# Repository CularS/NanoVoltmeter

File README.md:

# NanoVoltmeter
Low and high input resistance nanovoltmeter with 20 and 200 mV range

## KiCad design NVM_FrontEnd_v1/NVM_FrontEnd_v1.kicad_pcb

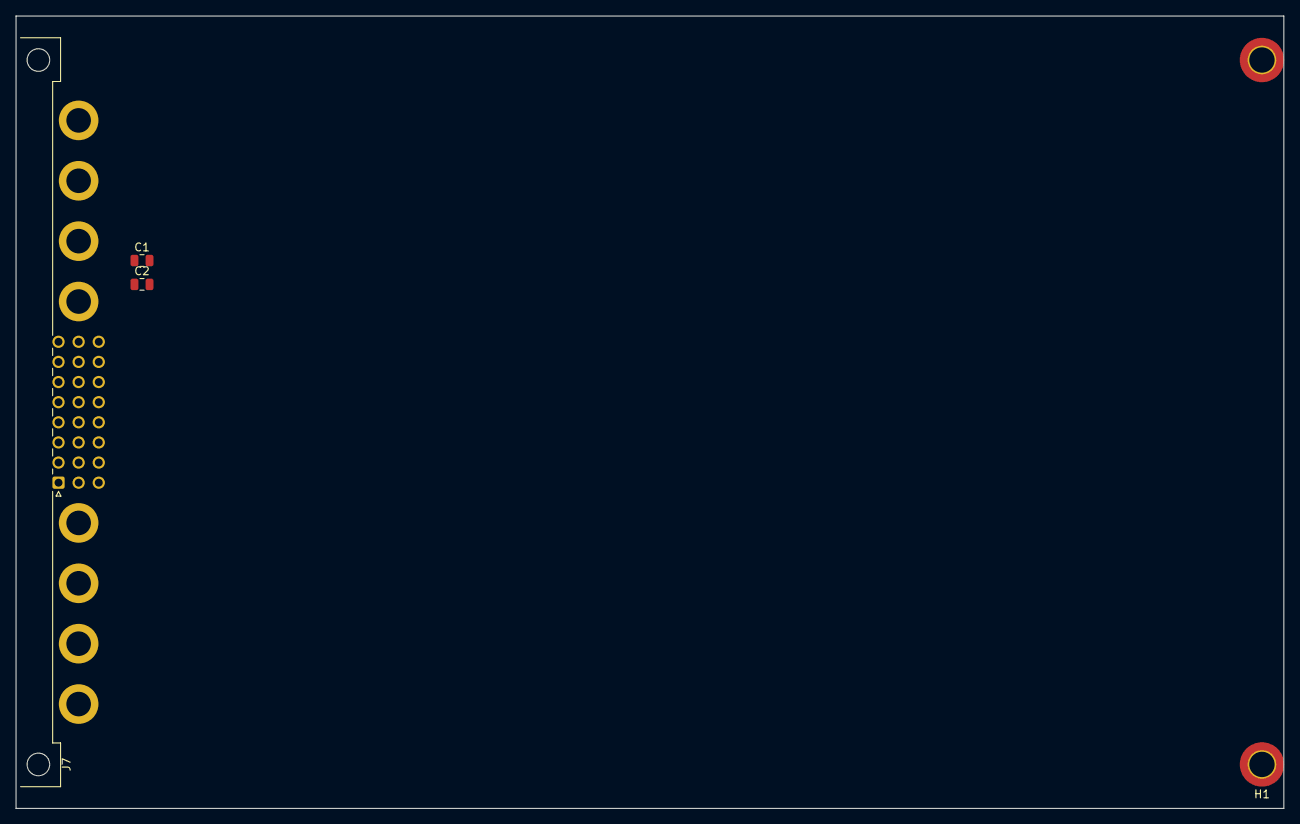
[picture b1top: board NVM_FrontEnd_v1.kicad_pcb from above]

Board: 2 copper layers, 160.0 x 100.0 mm, 5 parts (0 on the bottom side), 5 nets, no tracks yet.

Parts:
C1, C2: 10u; C_0805_2012Metric
H1, H3: MountingHole_Pad; MountingHole_3.2mm_M3_DIN965_Pad_TopBottom
J7: DIN41612_M_3x8+8_Power_Male; DIN41612_M_3x8+8_Male_Horizontal_THT_Power

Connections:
+5V_An: C2.1, J7.P3
+5V_Dig: C1.1, J7.P7
DGND: C1.2, J7.P6, J7.P8
Earth: H1.1 (1_1), H3.1 (1_1)
STAR: C2.2, J7.P2, J7.P5

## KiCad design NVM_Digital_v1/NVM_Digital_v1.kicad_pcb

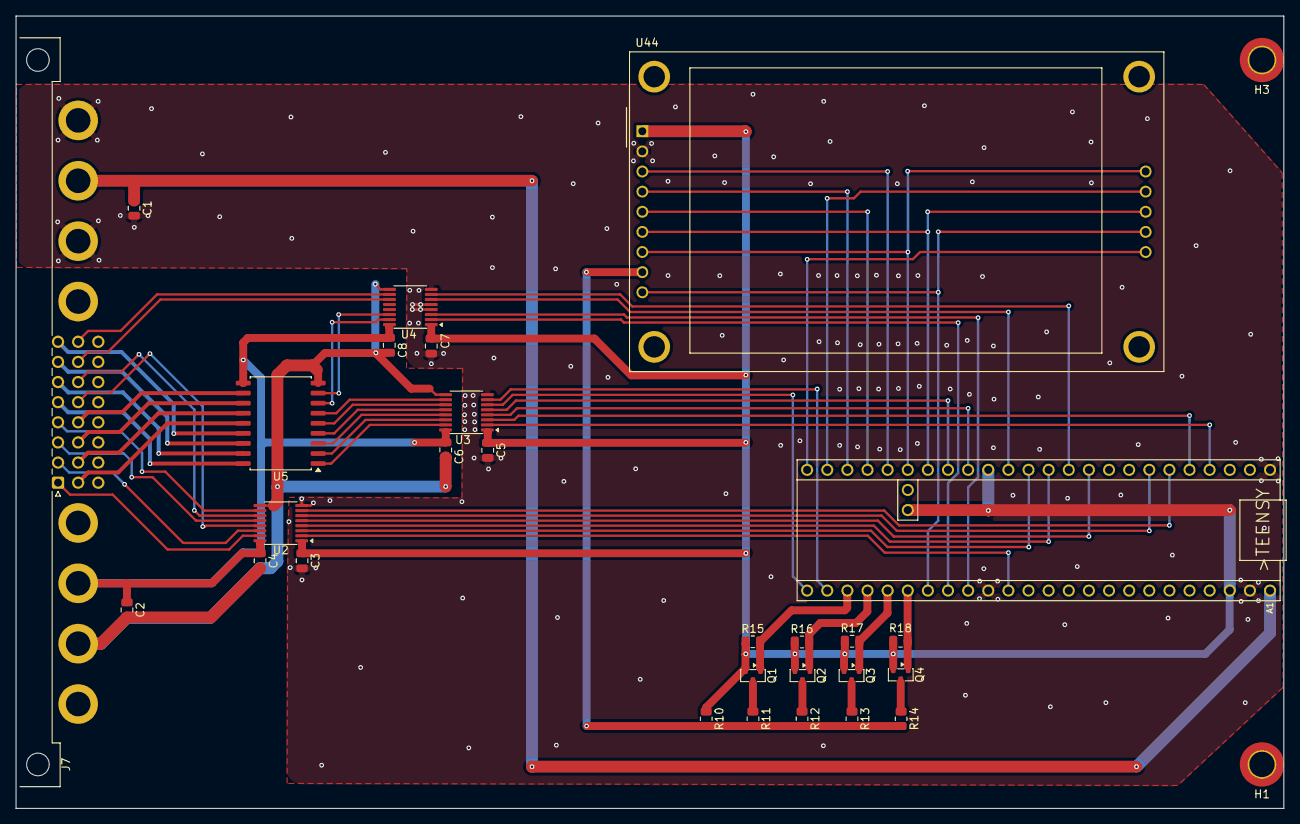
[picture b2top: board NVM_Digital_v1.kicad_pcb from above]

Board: 2 copper layers, 160.0 x 100.0 mm, 30 parts (0 on the bottom side), 63 nets.

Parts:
A1: TEENSY_4.1; TEENSY_LONG_EXT
C1, C2: 10u; C_0805_2012Metric
C3, C4, C5, C6, C7, C8: 100n; C_0805_2012Metric
H1, H3: MountingHole_Pad; MountingHole_3.2mm_M3_DIN965_Pad_TopBottom
J7: DIN41612_M_3x8+8_Power_Male; DIN41612_M_3x8+8_Male_Horizontal_THT_Power
Q1, Q2, Q3, Q4: DMG3415U; SOT-23
R10: 330R; R_0805_2012Metric
R11: 150R; R_0805_2012Metric
R12: 68R; R_0805_2012Metric
R13: 33R; R_0805_2012Metric
R14: 15R; R_0805_2012Metric
R15, R16, R17, R18: 100k; R_0805_2012Metric
U2: ISO7760F SPI/CTRL; QSOP-16_3.9x4.9mm_P0.635mm
U3: ISO7760F COILS 1-6; QSOP-16_3.9x4.9mm_P0.635mm
U4: ISO7762F COILS+RD; QSOP-16_3.9x4.9mm_P0.635mm
U5: TBD62083AFWG; SOP-18_7.495x11.515mm_P1.27mm
U44: CR2013-MI2120

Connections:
+3V3: A1.3V3 (3.3V), A1.3V3@2 (3.3V), A1.3V3@3 (3.3V), C3.1, C5.1, C7.1, Q1.2 (S), Q2.2 (S), Q3.2 (S), Q4.2 (S), R10.1, R15.1, R16.1, R17.1, R18.1, U2.1 (Vcc1), U3.1 (Vcc1), U4.1 (Vcc1), U44.1 (VCC)
+5V_An: C2.1, C4.1, C6.1, C8.1, J7.P3, U2.16 (Vcc2), U3.16 (Vcc2), U4.16 (Vcc2), U5.10 (COM)
+5V_Dig: A1.VIN, C1.1, J7.P7
ADC_BUSY: J7.b20, U4.10 (INF)
ADC_CS: J7.b17, U2.13 (OUTC)
ADC_MCLK: J7.b18, U2.11 (OUTE)
ADC_SDO: J7.b19, U4.11 (INE)
CHOP_L: J7.a17, U5.18 (O1)
CHOP_LOG: U3.15 (OUTA), U5.1 (I1)
DGND: A1.AGND/GND (GND), A1.GND, A1.GND@2 (GND), C1.2, C3.2, C5.2, C7.2, J7.P6, J7.P8, U2.8 (GND1), U3.8 (GND1), U4.4 (INC), U4.5 (IND), U4.8 (GND1), U44.2 (GND)
D_ADC_BUSY: A1.D9, U4.7 (OUTF)
D_ADC_CS: A1.D10 ((CS)D10), U2.4 (INC)
D_ADC_MCLK: A1.D5, U2.6 (INE)
D_BL1: A1.D35, Q1.1 (G), R15.2
D_BL2: A1.D36, Q2.1 (G), R16.2
D_BL3: A1.D37, Q3.1 (G), R17.2
D_BL4: A1.D38 (A14), Q4.1 (G), R18.2
D_CHOP: A1.D2, U3.2 (INA)
D_DAC_CS: A1.D8, U2.5 (IND)
D_DAC_RST: A1.D4, U2.7 (INF)
D_K3R: A1.D25 (A11), U3.5 (IND)
D_K3S: A1.D24 (A10), U3.4 (INC)
D_K4R: A1.D34, U3.7 (INF)
D_K4S: A1.D33, U3.6 (INE)
D_K5R: A1.D41 (A17), U4.3 (INB)
D_K5S: A1.D40 (A16), U4.2 (INA)
D_MISO: A1.D12 ((SDI)D12), U4.6 (OUTE)
D_MOSI: A1.D11 ((SDO)D11), U2.3 (INB)
D_RANGE: A1.D3, U3.3 (INB)
D_SCK: A1.D13 ((CLK)D13), U2.2 (INA)
Earth: H1.1 (1_1), H3.1 (1_1)
K3R_L: U3.12 (OUTD), U5.4 (I4)
K3S_L: U3.13 (OUTC), U5.3 (I3)
K3_RST: J7.a20, U5.15 (O4)
K3_SET: J7.a19, U5.16 (O3)
K4R_L: U3.10 (OUTF), U5.6 (I6)
K4S_L: U3.11 (OUTE), U5.5 (I5)
K4_RST: J7.b14, U5.13 (O6)
K4_SET: J7.b13, U5.14 (O5)
K5R_L: U4.14 (OUTB), U5.8 (I8)
K5S_L: U4.15 (OUTA), U5.7 (I7)
K5_RST: J7.b16, U5.11 (O8)
K5_SET: J7.b15, U5.12 (O7)
unnamed: Q1.3 (D), R11.1
unnamed: Q2.3 (D), R12.1
unnamed: Q3.3 (D), R13.1
unnamed: Q4.3 (D), R14.1
unnamed: R10.2, R11.2, R12.2, R13.2, R14.2, U44.8 (LED)
RANGE_L: J7.a18, U5.17 (O2)
RANGE_LOG: U3.14 (OUTB), U5.2 (I2)
RESET_N: J7.a16, U2.10 (OUTF)
SCLK: J7.a13, U2.15 (OUTA)
SDIN: J7.a14, U2.14 (OUTB)
SPI1_MISO: A1.D39 (A15), U44.9 (MISO), U44.13 (T_DO)
SPI1_MOSI: A1.D26 (A12), U44.6 (MOSI), U44.12 (T_DIN)
SPI1_SCK: A1.D27 (A13), U44.7 (SCK), U44.10 (T_CLK)
STAR: C2.2, C4.2, C6.2, C8.2, J7.P2, J7.P5, U2.9 (GND2), U3.9 (GND2), U4.9 (GND2), U5.9 (GND)
SYNC_N: J7.a15, U2.12 (OUTD)
TFT_CS: A1.D28, U44.3 (~CS)
TFT_DC: A1.D29, U44.5 (D/~C)
TFT_RST: A1.D30, U44.4 (RESET)
T_CS: A1.D31, U44.11 (T_CS)
T_IRQ: A1.D32, U44.14 (T_IRQ)

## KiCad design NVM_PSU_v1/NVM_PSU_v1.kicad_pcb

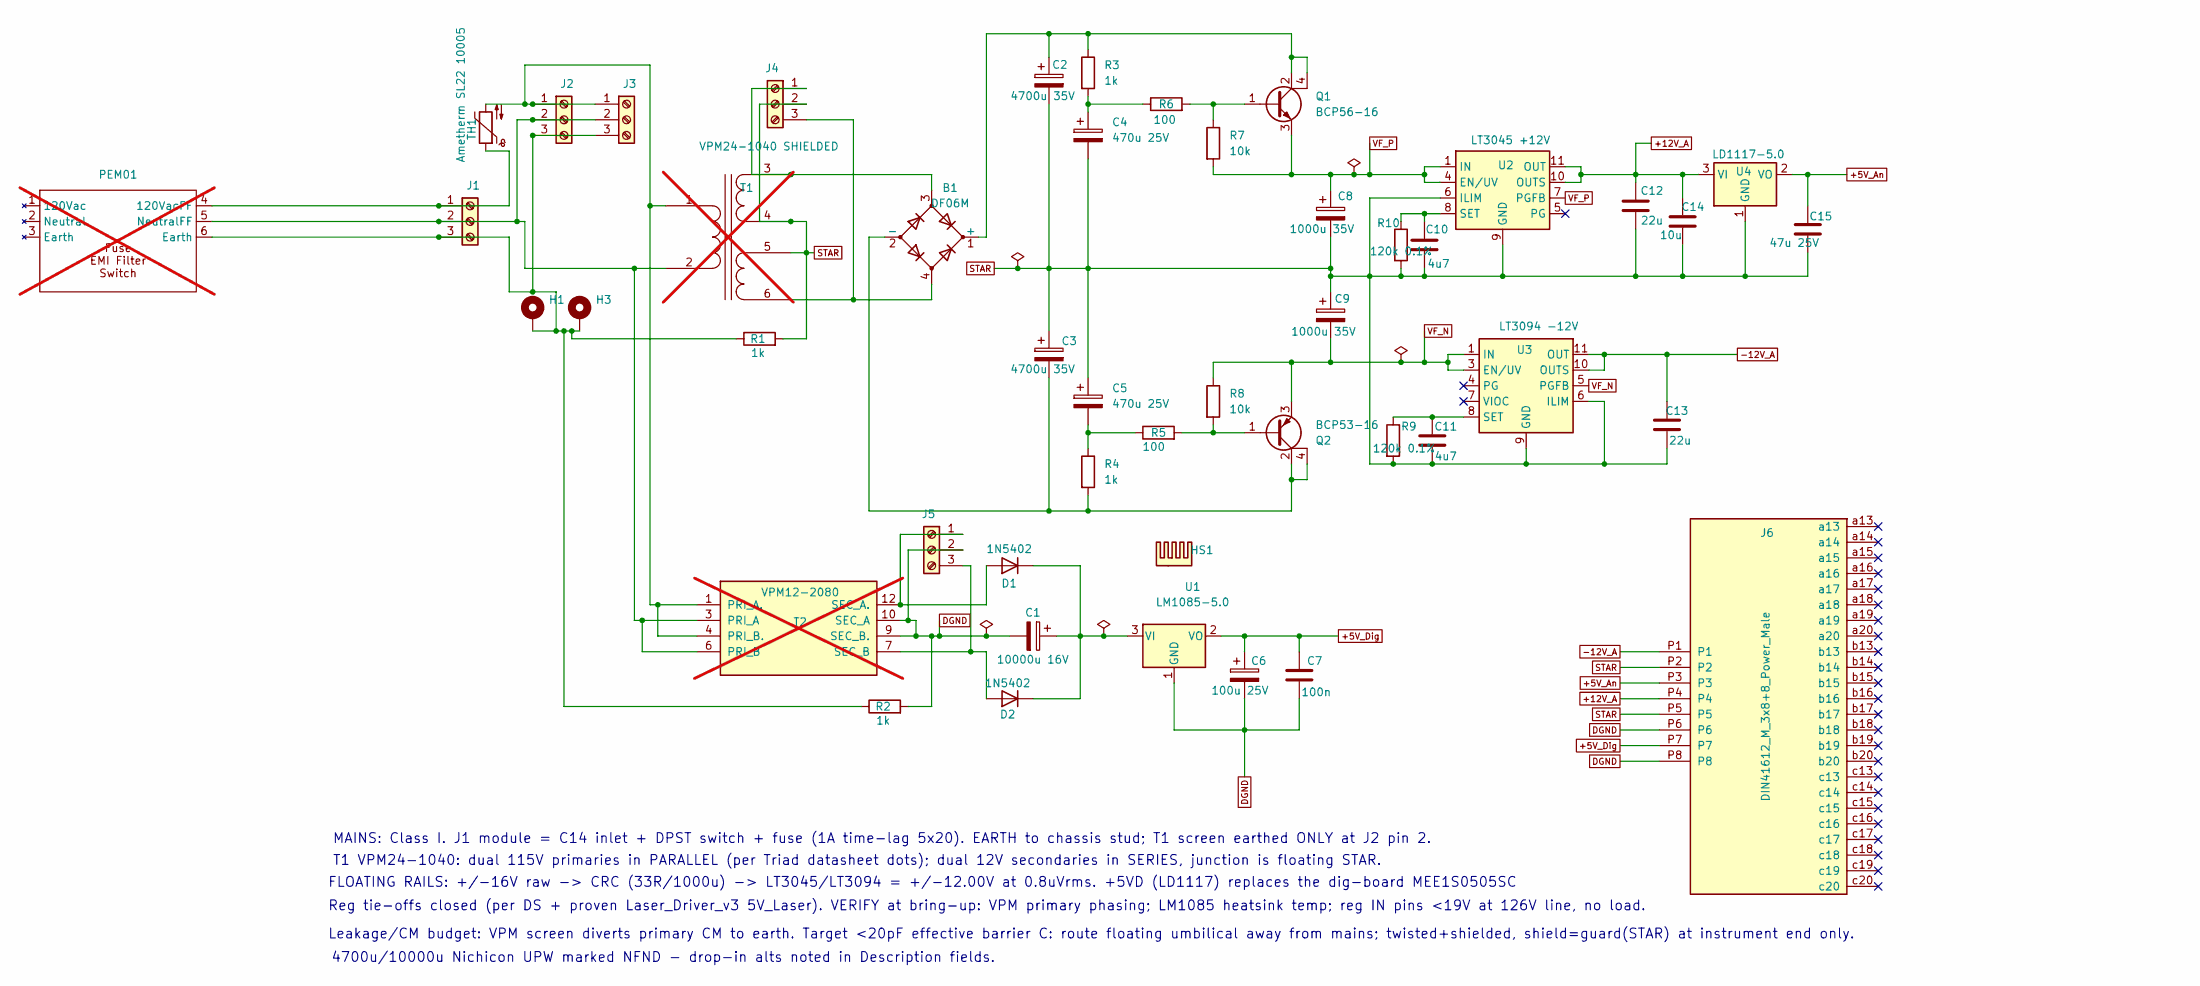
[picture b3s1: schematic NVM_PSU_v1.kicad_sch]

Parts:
B1: DF06M; Diode_Bridge_DIP-4_W7.62mm_P5.08mm; MPN DF06M-E3/45; DigiKeyPN DF06M-E3/45GICT-ND
C1: 10000u 16V; CP_Radial_D18.0mm_P7.50mm; MPN UPW1C103MHD; DigiKeyPN 493-1638-ND
C2, C3: 4700u 35V; CP_Radial_D18.0mm_P7.50mm; MPN UPW1V472MHD; DigiKeyPN 493-1653-ND
C4, C5: 470u 25V; CP_Radial_D10.0mm_P5.00mm; MPN ECA-1EM471
C6: 100u 25V; CP_Radial_D8.0mm_P3.50mm; MPN UPW1E101MED; DigiKeyPN 493-1548-ND
C7: 100n; C_0805_2012Metric; MPN GRM21BR71H104KA01L
C8, C9: 1000u 35V; CP_Radial_D12.5mm_P5.00mm; MPN UPW1V102MHD; DigiKeyPN 493-1645-ND
C10, C11: 4u7; C_0805_2012Metric; MPN GRM21BR71E475KE13L
C12, C13: 22u; C_0805_2012Metric; MPN GRM21BR61E226ME44L
C14: 10u; C_0805_2012Metric; MPN GRM21BR61E106KA73L
C15: 47u 25V; CP_Radial_D5.0mm_P2.00mm; MPN ECA-1EM470
D1, D2: 1N5402; D_DO-201AD_P12.70mm_Horizontal; MPN 1N5402G; DigiKeyPN 1N5402GOS-ND
H1, H3: MountingHole_Pad; MountingHole_3.2mm_M3_DIN965_Pad_TopBottom
HS1: AAVID 531102B02500G; Heatsink_AAVID_Extruded_531102B02500G_34.9x12.7mm_H38.1mm; MPN 531102B02500G; DigiKeyPN HS352-ND
J1, J2, J3, J4, J5: Screw_Terminal_01x03; TerminalBlock_Phoenix_MKDS-1,5-3-5.08_1x03_P5.08mm_Horizont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; MPN 1729131
J6: DIN41612_M_3x8+8_Power_Male; DIN41612_M_3x8+8_Male_Horizontal_THT_Power
PEM01: not fitted
Q1: BCP56-16; SOT-223; MPN BCP56-16TF
Q2: BCP53-16; SOT-223; MPN BCP53-16TF
R1, R2, R3, R4: 1k; R_0805_2012Metric_Pad1.20x1.40mm_HandSolder; MPN CRCW08051K00FKEA
R5, R6: 100; R_0805_2012Metric_Pad1.20x1.40mm_HandSolder; MPN RC0805FR-07100RL
R7, R8: 10k; R_0805_2012Metric_Pad1.20x1.40mm_HandSolder; MPN RC0805FR-0710KL
R9, R10: 120k 0.1%; R_0805_2012Metric; MPN RT0805BRD07120KL
T1: VPM24-1040 SHIELDED; WirePad_1x06_P7.62; MPN VPM24-1040; DigiKeyPN 237-2025-ND; not fitted
T2: VPM12-2080; MPN VPM12-2080; DigiKeyPN 237-2023-ND; not fitted
TH1: Ametherm SL22 10005; R_Axial_DIN0411_L9.9mm_D3.6mm_P7.62mm_Vertical
U1: LM1085-5.0; TO-220-3_Vertical; MPN LM1085IT-5.0/NOPB; DigiKeyPN LM1085IT-5.0/NOPB-ND
U2: LT3045 +12V; MSOP-12-1EP_3x4.039mm_P0.65mm_EP1.651x2.845mm; MPN LT3045EMSE#PBF; DigiKeyPN LT3045EMSE#PBF-ND
U3: LT3094 -12V; MSOP-12-1EP_3x4.039mm_P0.65mm_EP1.651x2.845mm; MPN LT3094EMSE#TRPBF; DigiKeyPN LT3094EMSE#TRPBF-ND
U4: LD1117-5.0; SOT-223-3_TabPin2; MPN LD1117S50TR; DigiKeyPN 497-1440-2-ND

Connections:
+5V_An: C15.1, J6.P3, U4.2 (VO)
+5V_Dig: C6.1, C7.1, J6.P7, U1.2 (VO)
+12V_A: C12.1, C14.1, J6.P4, U2.10 (OUTS), U2.11 (OUT), U2.12 (OUT), U4.3 (VI)
-12V_A: C13.1, J6.P1, U3.10 (OUTS), U3.11 (OUT), U3.12 (OUT)
DGND: C1.2, C6.2, C7.2, J5.2, J6.P6, J6.P8, R2.2, T2.9 (SEC_B.), T2.10 (SEC_A), U1.1 (GND)
unnamed: B1.1 (+), C2.1, Q1.2 (C), Q1.4 (C), R3.1
unnamed: B1.2 (-), C3.2, Q2.2 (C), Q2.4 (C), R4.2
unnamed: C4.1, R3.2, R6.1
unnamed: C5.2, R4.1, R5.1
unnamed: D1.2 (A), J5.1, T2.12 (SEC_A.)
unnamed: C1.1, D1.1 (K), D2.1 (K), U1.3 (VI)
unnamed: D2.2 (A), J5.3, T2.7 (SEC_B)
unnamed: J1.1, PEM01.4 (120VacFF), TH1.1
unnamed: J1.2, J2.2, J3.2, PEM01.5 (NeutralFF), T1.2 (AB), T2.3 (PRI_A), T2.6 (PRI_B)
unnamed: H1.1 (1_1), H3.1 (1_1), J1.3, J2.3, J3.3, PEM01.6 (Earth), R1.1, R2.1
unnamed: J2.1, J3.1, T1.1 (AA), T2.1 (PRI_A.), T2.4 (PRI_B.), TH1.2
unnamed: B1.3, J4.1, T1.3 (SA)
unnamed: B1.4, J4.3, T1.6 (SD)
unnamed: Q1.1 (B), R6.2, R7.1
unnamed: Q2.1 (B), R5.2, R8.2
unnamed: C10.1, R10.1, U2.8 (SET)
unnamed: C11.1, R9.1, U3.8 (SET)
STAR: C2.2, C3.1, C4.2, C5.1, C8.2, C9.1, C10.2, C11.2, C12.2, C13.2, C14.2, C15.2, J4.2, J6.P2, J6.P5, R1.2, R9.2, R10.2, T1.4 (SB), T1.5 (SC), U2.6 (ILIM), U2.9 (GND), U2.13 (GND), U3.6 (ILIM), U3.9 (GND), U4.1 (GND)
VF_N: C9.2, Q2.3 (E), R8.1, U3.1 (IN), U3.2 (IN), U3.3 (EN/UV), U3.5 (PGFB), U3.13 (IN)
VF_P: C8.1, Q1.3 (E), R7.2, U2.1 (IN), U2.2 (IN), U2.3 (IN), U2.4 (EN/UV), U2.7 (PGFB)

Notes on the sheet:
T1 VPM24-1040: dual 115V primaries in PARALLEL (per Triad datasheet dots); dual 12V secondaries in SERIES, junction is floating STAR.
4700u/10000u Nichicon UPW marked NFND - drop-in alts noted in Description fields.
MAINS: Class I. J1 module = C14 inlet + DPST switch + fuse (1A time-lag 5x20). EARTH to chassis stud; T1 screen earthed ONLY at J2 pin 2.
Leakage/CM budget: VPM screen diverts primary CM to earth. Target <20pF effective barrier C: route floating umbilical away from mains; twisted+shielded, shield=guard(STAR) at instrument end only.
FLOATING RAILS: +/-16V raw -> CRC (33R/1000u) -> LT3045/LT3094 = +/-12.00V at 0.8uVrms. +5VD (LD1117) replaces the dig-board MEE1S0505SC
Reg tie-offs closed (per DS + proven Laser_Driver_v3 5V_Laser). VERIFY at bring-up: VPM primary phasing; LM1085 heatsink temp; reg IN pins <19V at 126V line, no load.

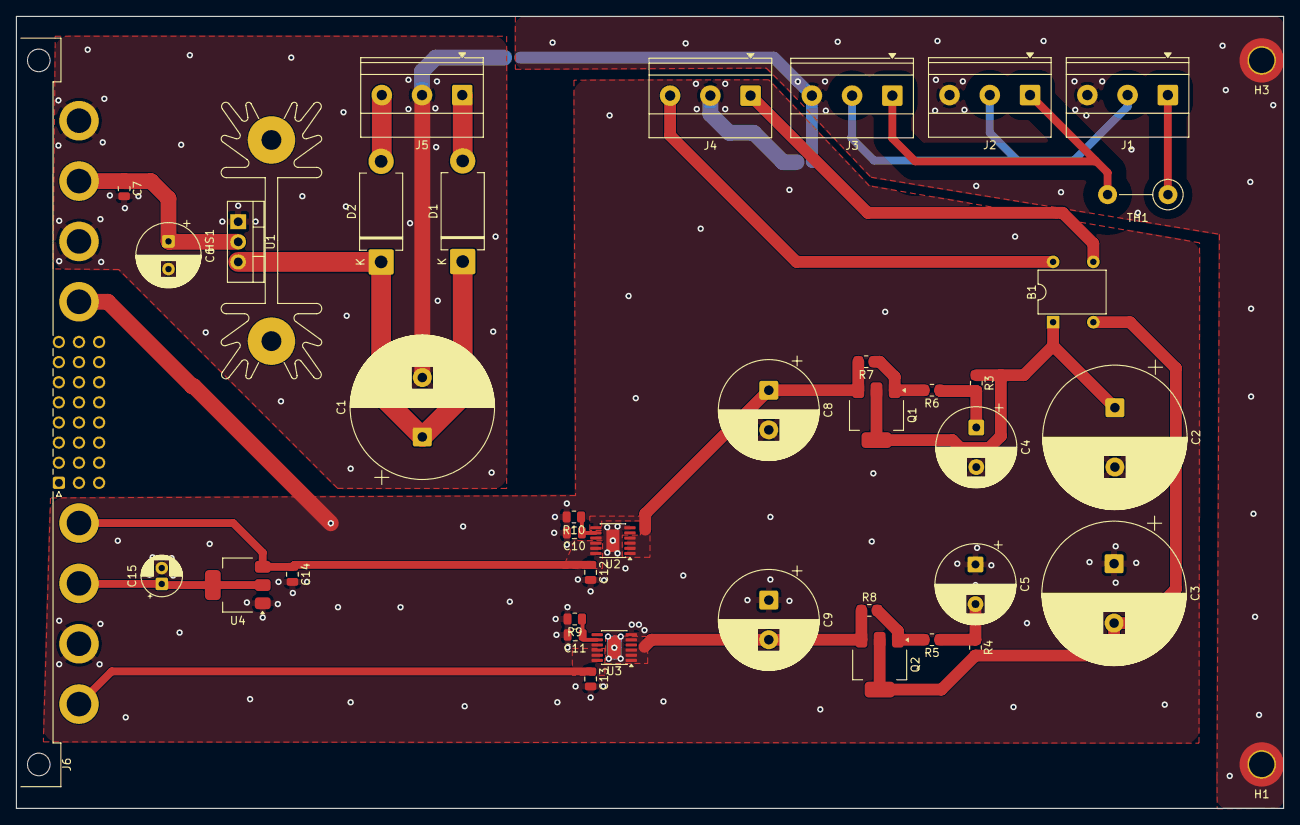
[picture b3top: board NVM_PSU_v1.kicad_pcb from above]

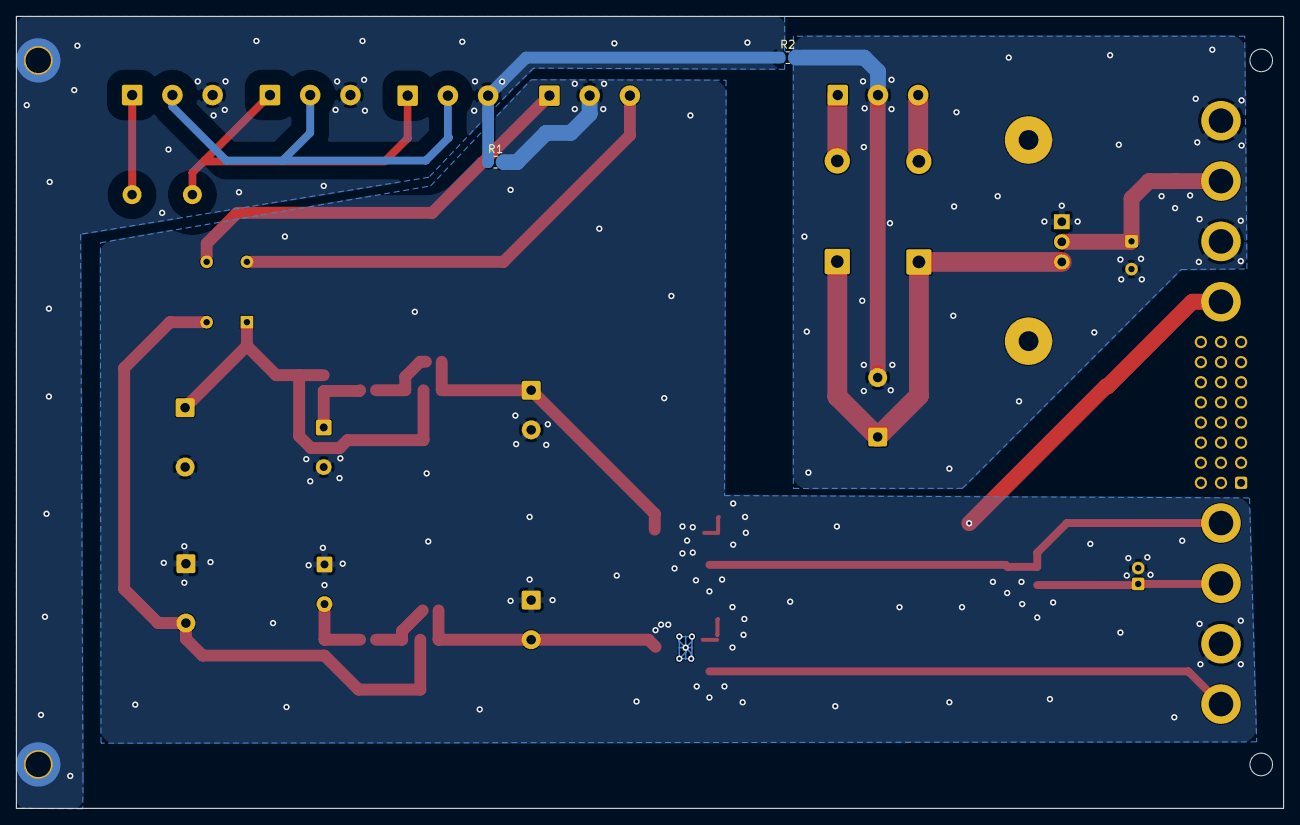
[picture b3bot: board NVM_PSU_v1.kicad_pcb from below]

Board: 2 copper layers, 160.0 x 100.0 mm, 44 parts (2 on the bottom side), 25 nets.

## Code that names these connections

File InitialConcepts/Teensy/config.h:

#pragma once

// ============================================================
// Nanovoltmeter controller — Teensy 4.1
//
// Front end: see Nanovoltmeter/nanovoltmeter_fe.kicad_sch
//   K1 chop relay (polarity reversal), K2 range (G=201 / G=21),
//   K3 input short (auto-zero / blanking), K4 100k bias-cal std,
//   AD5689R bias-current servo DAC, LTC2500-32 ADC on VOUT.
//
// All relay coils are driven through digital isolators + ULN2003
// on the digital side (J3 of the front end). ADC/DAC SPI crosses
// the same isolation barrier.
//
// DEMO MODE (runtime, EEPROM-persisted, 'demo on'/'demo off'):
// full firmware runs against a simulated front end — UI, network,
// measurement engine and cal routines all testable with only a
// Teensy + TFT on the bench.
// ============================================================

#define DEMO_MODE_DEFAULT   1   // first-boot default: 1 = demo on

// ------------------------------------------------------------
// Pin map — Teensy 4.1
// SPI0 (11/12/13): LTC2500-32 ADC + AD5689R DAC (isolated bus)
// SPI1 (26/27):    ILI9341 TFT (same wiring as dual-PDH build)
// ------------------------------------------------------------

// --- SPI0 (measurement bus) ---------------------------------
#define PIN_MOSI          11
#define PIN_MISO          12
#define PIN_SCK           13

#define PIN_ADC_CS        10   // LTC2500-32 chip select
#define PIN_ADC_BUSY       9   // LTC2500-32 BUSY/DRDY (high while converting)
#define PIN_ADC_MCLK       5   // conversion strobe (IntervalTimer-driven)

#define PIN_DAC_CS         8   // AD5689R SYNC
#define PIN_DAC_RST        4   // AD5689R /RESET (drive HIGH for normal run)

// --- Switch drives (via isolators + TBD62083, active HIGH) ------
// SSR LEVEL lines (PhotoMOS chop bridge + range select on the FE;
// Teensy HIGH -> driver sinks the pulled-up FE line LOW):
#define PIN_CHOP           2   // HIGH = reversed polarity, LOW = forward
#define PIN_RANGE          3   // HIGH = G=21 (200 mV), LOW = G=201 (20 mV)
// Latching 2-coil mechanical relays: pulse SET or RESET, never hold.
#define PIN_K3_SET        24   // short: SET = input shorted
#define PIN_K3_RST        25
#define PIN_K4_SET        33   // cal:   SET = 100k across input
#define PIN_K4_RST        34
#define PIN_K5_SET        40   // mode:  SET = SSR chop bridge in path (low-Z)
#define PIN_K5_RST        41   //        RESET = source direct (high-Z)

// --- Front-panel buttons (active LOW, internal pullups) -----
#define PIN_BTN_TAB       35   // cycle Operation / Settings / Calibration
#define PIN_BTN_UP        36
#define PIN_BTN_DOWN      37
#define PIN_BTN_SEL       38

// --- SPI1 (display) — identical to dual-PDH controller ------
#define PIN_TFT_MOSI      26
#define PIN_TFT_SCK       27
#define PIN_TFT_CS        28
#define PIN_TFT_DC        29
#define PIN_TFT_RST       30
// XPT2046 resistive touch, shared SPI1. T_DO must be wired to
// pin 39 (SPI1 MISO) — the TFT itself never drives MISO.
#define PIN_TOUCH_CS      31
#define PIN_TOUCH_IRQ     32

// Touch calibration — raw ADC extents mapped to the 320x240
// landscape screen. Tune with the 'touch' CLI command at
// bring-up (tap corners, adjust until mapped x/y match).
#define TS_RAW_MIN       250
#define TS_RAW_MAX      3850
#define TS_SWAP_XY         1   // raw axes are portrait on most modules
#define TS_FLIP_X          0
#define TS_FLIP_Y          1
#define TS_DEBOUNCE_MS   250   // min interval between accepted taps

// ------------------------------------------------------------
// Relay timing
// ------------------------------------------------------------
#define RELAY_PULSE_MS      10   // latching coil pulse width
#define RELAY_GAP_MS        10   // gap between queued coil pulses

// ------------------------------------------------------------
// ADC — LTC2500-32, sinc filter, line-synchronous rates
// MCLK 15360 Hz / DF 256  -> 60 filtered samples/s, nulls at n*60 Hz.
// For 50 Hz mains use 12800 Hz / DF 256 -> 50 SPS.       (VERIFY vs datasheet)
// ------------------------------------------------------------
#define ADC_MCLK_HZ       15360
#define ADC_DF              256
#define ADC_VREF            5.0f     // LTC2500 REF pin (from front-end reference)
#define ADC_FS_CODE         (2147483648.0)  // 2^31 (32-bit signed full scale)
#define ADC_OVERLOAD_FRAC   0.95f    // |code| above this fraction of FS = overload

// ------------------------------------------------------------
// Front-end constants (nominal; corrected by cal factors)
// ------------------------------------------------------------
#define GAIN_20MV_NOM     201.0f     // K2 RESET: 2x1k over 10R
#define GAIN_200MV_NOM     21.0f     // K2 SET:   2x1k over 100R
#define RANGE_20MV_FS     0.020f     // volts, nominal input full scale
#define RANGE_200MV_FS    0.200f

#define BIAS_DAC_BITS     16
// Bipolar servo: DAC A -> x-2 inverter -> 10G sinks up to 1 nA
// (gate leakage sources current INTO the node); DAC B -> 10G
// sources up to +500 pA for the opposite-polarity case.
#define BIAS_NEG_FULL_PA 1000.0f
#define BIAS_POS_FULL_PA  500.0f
#define CAL_RES_OHM       100e3f     // K4 bias-cal standard (Y0007 100k)

// ------------------------------------------------------------
// Measurement engine defaults (all runtime-adjustable, persisted)
// SSR chop switches in us, so fast chop (>= LSK389 1/f corner)
// is available: 20 ms half = 25 Hz full cycle.
// ------------------------------------------------------------
#define DEF_CHOP_HALF_MS    20       // chop half-period (25 Hz full cycle)
#define CHOP_BLANK_MS        4       // discard after an SSR chop flip
#define DEF_SETTLE_MS      100       // discard after a mechanical relay change
#define DEF_APERTURE_MS   1000       // high-Z mode integration per reading
#define DEF_AZ_INTERVAL_S   30       // high-Z auto-zero spacing (0 = off)
#define AUTORANGE_UP_FRAC  0.90f     // uprange above this fraction of FS
#define AUTORANGE_DN_FRAC  0.08f     // downrange below this fraction of FS

// Bias-cal servo
#define BIASCAL_TOL_V      3e-7f     // stop when |V(100k)| < 300 nV (3 pA)
#define BIASCAL_MAX_ITER   24
#define BIASCAL_SETTLE_MS  3000      // 10G x filter needs seconds to settle

// ------------------------------------------------------------
// Timing
// ------------------------------------------------------------
#define CONTROL_PERIOD_US 1000UL     // 1 kHz engine tick
#define DISPLAY_PERIOD_MS  100UL     // 10 Hz UI + network poll
#define DEBUG_PERIOD_MS   2000UL
